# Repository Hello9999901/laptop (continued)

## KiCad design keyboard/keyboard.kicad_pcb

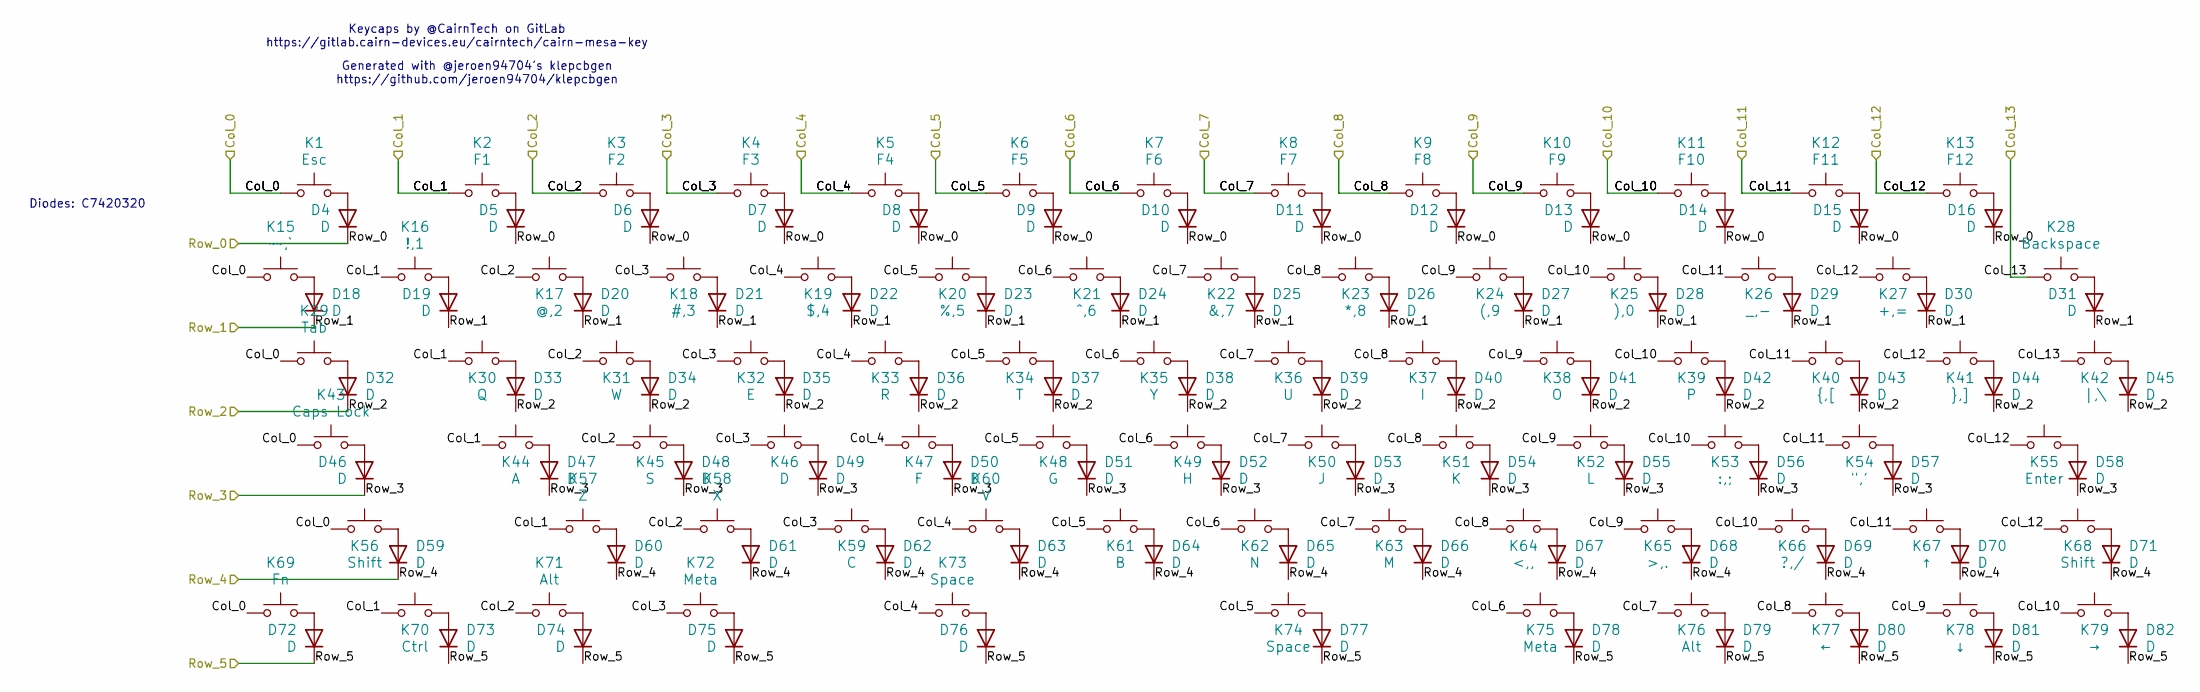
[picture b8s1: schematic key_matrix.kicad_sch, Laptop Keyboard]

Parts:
D4, D5, D6, D7, D8, D9, D10, D11, D12, D13, D14, D15, D16, D18, D19, D20, D21, D22, D23, D24, D25, D26, D27, D28, D29, D30, D31, D32, D33, D34, D35, D36, D37, D38, D39, D40, D41, D42, D43, D44, D45, D46, D47, D48, D49, D50, D51, D52, D53, D54, D55, D56, D57, D58, D59, D60, D61, D62, D63, D64, D65, D66, D67, D68, D69, D70, D71, D72, D73, D74, D75, D76, D77, D78, D79, D80, D81, D82: D; D_SOD-523
K1: Esc; Cherry_ULP_SMD
K2: F1; Cherry_ULP_SMD
K3: F2; Cherry_ULP_SMD
K4: F3; Cherry_ULP_SMD
K5: F4; Cherry_ULP_SMD
K6: F5; Cherry_ULP_SMD
K7: F6; Cherry_ULP_SMD
K8: F7; Cherry_ULP_SMD
K9: F8; Cherry_ULP_SMD
K10: F9; Cherry_ULP_SMD
K11: F10; Cherry_ULP_SMD
K12: F11; Cherry_ULP_SMD
K13: F12; Cherry_ULP_SMD
K15: ~~,`; Cherry_ULP_SMD
K16: !,1; Cherry_ULP_SMD
K17: @,2; Cherry_ULP_SMD
K18: #,3; Cherry_ULP_SMD
K19: $,4; Cherry_ULP_SMD
K20: %,5; Cherry_ULP_SMD
K21: ^,6; Cherry_ULP_SMD
K22: &,7; Cherry_ULP_SMD
K23: *,8; Cherry_ULP_SMD
K24: (,9; Cherry_ULP_SMD
K25: ),0; Cherry_ULP_SMD
K26: _,-; Cherry_ULP_SMD
K27: +,=; Cherry_ULP_SMD
K28: Backspace; Cherry_ULP_SMD
K29: Tab; Cherry_ULP_SMD
K30: Q; Cherry_ULP_SMD
K31: W; Cherry_ULP_SMD
K32: E; Cherry_ULP_SMD
K33: R; Cherry_ULP_SMD
K34: T; Cherry_ULP_SMD
K35: Y; Cherry_ULP_SMD
K36: U; Cherry_ULP_SMD
K37: I; Cherry_ULP_SMD
K38: O; Cherry_ULP_SMD
K39: P; Cherry_ULP_SMD
K40: {,[; Cherry_ULP_SMD
K41: },]; Cherry_ULP_SMD
K42: |,\; Cherry_ULP_SMD
K43: Caps Lock; Cherry_ULP_SMD
K44: A; Cherry_ULP_SMD
K45: S; Cherry_ULP_SMD
K46: D; Cherry_ULP_SMD
K47: F; Cherry_ULP_SMD
K48: G; Cherry_ULP_SMD
K49: H; Cherry_ULP_SMD
K50: J; Cherry_ULP_SMD
K51: K; Cherry_ULP_SMD
K52: L; Cherry_ULP_SMD
K53: :,;; Cherry_ULP_SMD
K54: ",'; Cherry_ULP_SMD
K55: Enter; Cherry_ULP_SMD
K56, K68: Shift; Cherry_ULP_SMD
K57: Z; Cherry_ULP_SMD
K58: X; Cherry_ULP_SMD
K59: C; Cherry_ULP_SMD
K60: V; Cherry_ULP_SMD
K61: B; Cherry_ULP_SMD
K62: N; Cherry_ULP_SMD
K63: M; Cherry_ULP_SMD
K64: <,,; Cherry_ULP_SMD
K65: >,.; Cherry_ULP_SMD
K66: ?,/; Cherry_ULP_SMD
K67: ↑; Cherry_ULP_SMD
K69: Fn; Cherry_ULP_SMD
K70: Ctrl; Cherry_ULP_SMD
K71, K76: Alt; Cherry_ULP_SMD
K72, K75: Meta; Cherry_ULP_SMD
K73, K74: Space; Cherry_ULP_SMD
K77: ←; Cherry_ULP_SMD
K78: ↓; Cherry_ULP_SMD
K79: →; Cherry_ULP_SMD

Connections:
/Key Matrix/Col_0: K1.1, K15.1, K29.1, K43.1, K56.1, K69.1; also elsewhere on the board
/Key Matrix/Col_1: K2.1, K16.1, K30.1, K44.1, K57.1, K70.1; also elsewhere on the board
/Key Matrix/Col_2: K3.1, K17.1, K31.1, K45.1, K58.1, K71.1; also elsewhere on the board
/Key Matrix/Col_3: K4.1, K18.1, K32.1, K46.1, K59.1, K72.1; also elsewhere on the board
/Key Matrix/Col_4: K5.1, K19.1, K33.1, K47.1, K60.1, K73.1; also elsewhere on the board
/Key Matrix/Col_5: K6.1, K20.1, K34.1, K48.1, K61.1, K74.1; also elsewhere on the board
/Key Matrix/Col_6: K7.1, K21.1, K35.1, K49.1, K62.1, K75.1; also elsewhere on the board
/Key Matrix/Col_7: K8.1, K22.1, K36.1, K50.1, K63.1, K76.1; also elsewhere on the board
/Key Matrix/Col_8: K9.1, K23.1, K37.1, K51.1, K64.1, K77.1; also elsewhere on the board
/Key Matrix/Col_9: K10.1, K24.1, K38.1, K52.1, K65.1, K78.1; also elsewhere on the board
/Key Matrix/Col_10: K11.1, K25.1, K39.1, K53.1, K66.1, K79.1; also elsewhere on the board
/Key Matrix/Col_11: K12.1, K26.1, K40.1, K54.1, K67.1; also elsewhere on the board
/Key Matrix/Col_12: K13.1, K27.1, K41.1, K55.1, K68.1; also elsewhere on the board
/Key Matrix/Col_13: K28.1, K42.1; also elsewhere on the board
/Key Matrix/Row_0: D4.1 (K), D5.1 (K), D6.1 (K), D7.1 (K), D8.1 (K), D9.1 (K), D10.1 (K), D11.1 (K), D12.1 (K), D13.1 (K), D14.1 (K), D15.1 (K), D16.1 (K); also elsewhere on the board
/Key Matrix/Row_1: D18.1 (K), D19.1 (K), D20.1 (K), D21.1 (K), D22.1 (K), D23.1 (K), D24.1 (K), D25.1 (K), D26.1 (K), D27.1 (K), D28.1 (K), D29.1 (K), D30.1 (K), D31.1 (K); also elsewhere on the board
/Key Matrix/Row_2: D32.1 (K), D33.1 (K), D34.1 (K), D35.1 (K), D36.1 (K), D37.1 (K), D38.1 (K), D39.1 (K), D40.1 (K), D41.1 (K), D42.1 (K), D43.1 (K), D44.1 (K), D45.1 (K); also elsewhere on the board
/Key Matrix/Row_3: D46.1 (K), D47.1 (K), D48.1 (K), D49.1 (K), D50.1 (K), D51.1 (K), D52.1 (K), D53.1 (K), D54.1 (K), D55.1 (K), D56.1 (K), D57.1 (K), D58.1 (K); also elsewhere on the board
/Key Matrix/Row_4: D59.1 (K), D60.1 (K), D61.1 (K), D62.1 (K), D63.1 (K), D64.1 (K), D65.1 (K), D66.1 (K), D67.1 (K), D68.1 (K), D69.1 (K), D70.1 (K), D71.1 (K); also elsewhere on the board
/Key Matrix/Row_5: D72.1 (K), D73.1 (K), D74.1 (K), D75.1 (K), D76.1 (K), D77.1 (K), D78.1 (K), D79.1 (K), D80.1 (K), D81.1 (K), D82.1 (K); also elsewhere on the board
unnamed: D4.2 (A), K1.2
unnamed: D5.2 (A), K2.2
unnamed: D6.2 (A), K3.2
unnamed: D7.2 (A), K4.2
unnamed: D8.2 (A), K5.2
unnamed: D9.2 (A), K6.2
unnamed: D10.2 (A), K7.2
unnamed: D11.2 (A), K8.2
unnamed: D12.2 (A), K9.2
unnamed: D13.2 (A), K10.2
unnamed: D14.2 (A), K11.2
unnamed: D15.2 (A), K12.2
unnamed: D16.2 (A), K13.2
unnamed: D18.2 (A), K15.2
unnamed: D19.2 (A), K16.2
unnamed: D20.2 (A), K17.2
unnamed: D21.2 (A), K18.2
unnamed: D22.2 (A), K19.2
unnamed: D23.2 (A), K20.2
unnamed: D24.2 (A), K21.2
unnamed: D25.2 (A), K22.2
unnamed: D26.2 (A), K23.2
unnamed: D27.2 (A), K24.2
unnamed: D28.2 (A), K25.2
unnamed: D29.2 (A), K26.2
unnamed: D30.2 (A), K27.2
unnamed: D31.2 (A), K28.2
unnamed: D32.2 (A), K29.2
unnamed: D33.2 (A), K30.2
unnamed: D34.2 (A), K31.2
unnamed: D35.2 (A), K32.2
unnamed: D36.2 (A), K33.2
unnamed: D37.2 (A), K34.2
unnamed: D38.2 (A), K35.2
unnamed: D39.2 (A), K36.2
unnamed: D40.2 (A), K37.2
unnamed: D41.2 (A), K38.2
unnamed: D42.2 (A), K39.2
unnamed: D43.2 (A), K40.2
unnamed: D44.2 (A), K41.2
unnamed: D45.2 (A), K42.2
unnamed: D46.2 (A), K43.2
unnamed: D47.2 (A), K44.2
unnamed: D48.2 (A), K45.2
unnamed: D49.2 (A), K46.2
unnamed: D50.2 (A), K47.2
unnamed: D51.2 (A), K48.2
unnamed: D52.2 (A), K49.2
unnamed: D53.2 (A), K50.2
unnamed: D54.2 (A), K51.2
unnamed: D55.2 (A), K52.2
unnamed: D56.2 (A), K53.2
unnamed: D57.2 (A), K54.2
unnamed: D58.2 (A), K55.2
unnamed: D59.2 (A), K56.2
unnamed: D60.2 (A), K57.2
unnamed: D61.2 (A), K58.2
unnamed: D62.2 (A), K59.2
unnamed: D63.2 (A), K60.2
unnamed: D64.2 (A), K61.2
unnamed: D65.2 (A), K62.2
unnamed: D66.2 (A), K63.2
unnamed: D67.2 (A), K64.2
unnamed: D68.2 (A), K65.2
unnamed: D69.2 (A), K66.2
unnamed: D70.2 (A), K67.2
unnamed: D71.2 (A), K68.2
unnamed: D72.2 (A), K69.2
unnamed: D73.2 (A), K70.2
unnamed: D74.2 (A), K71.2
unnamed: D75.2 (A), K72.2
unnamed: D76.2 (A), K73.2
unnamed: D77.2 (A), K74.2
unnamed: D78.2 (A), K75.2
unnamed: D79.2 (A), K76.2
unnamed: D80.2 (A), K77.2
unnamed: D81.2 (A), K78.2
unnamed: D82.2 (A), K79.2

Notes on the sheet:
Diodes: C7420320
Generated with @jeroen94704's klepcbgen https://github.com/jeroen94704/klepcbgen
Keycaps by @CairnTech on GitLab https://gitlab.cairn-devices.eu/cairntech/cairn-mesa-key

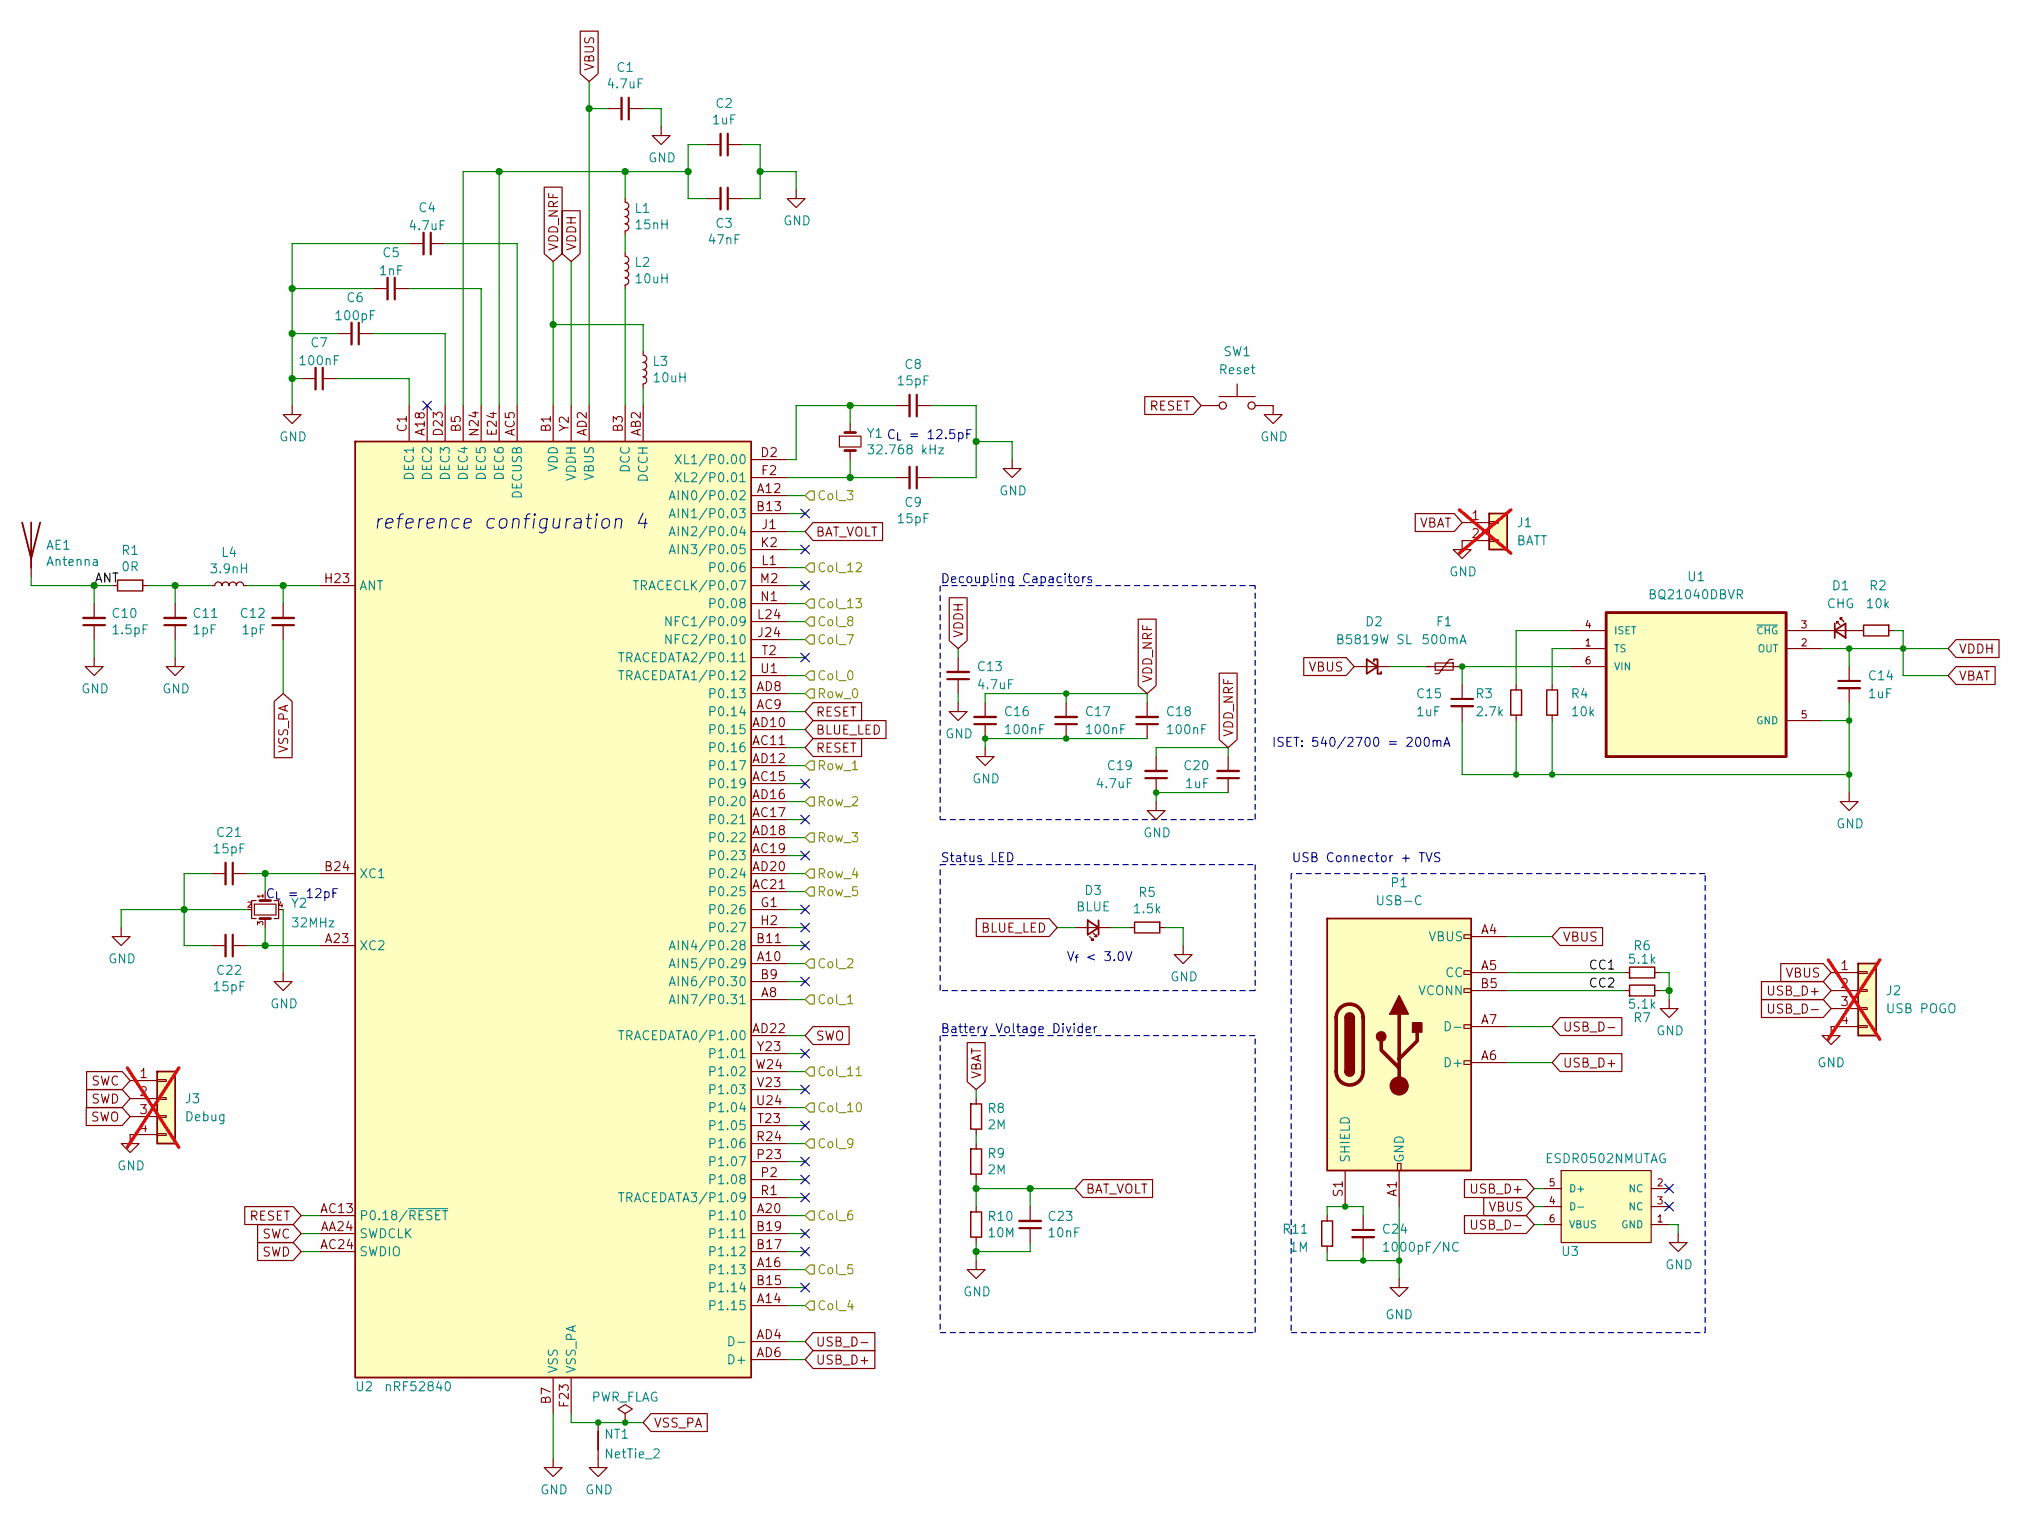
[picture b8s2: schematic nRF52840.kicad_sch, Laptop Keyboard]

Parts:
AE1: Antenna; 2.4GHz-meander-antenna-v2
C1, C4, C13, C19: 4.7uF; C_0402_1005Metric; Manufacturer Part CL05A475KP5NRNC; LCSC Part C368809
C2, C14, C15, C20: 1uF; C_0402_1005Metric; Manufacturer Part CL05A105KO5NNNC; LCSC Part C52923
C3: 47nF; C_0402_1005Metric; Manufacturer Part CL05B473KO5NNNC; LCSC Part C307434
C5: 1nF; C_0402_1005Metric; Manufacturer Part CL05B102KB5NNNC; LCSC Part C14442
C6: 100pF; C_0402_1005Metric; Manufacturer Part CL05C101JB5NNNC; LCSC Part C26409
C7, C16, C17, C18: 100nF; C_0402_1005Metric; Manufacturer Part CL05B104KA5NNNC; LCSC Part C1525
C8, C9, C21, C22: 15pF; C_0402_1005Metric; Manufacturer Part CL05C150JB51PNC; LCSC Part C307341
C10: 1.5pF; C_0402_1005Metric; Manufacturer Part CL05C1R5CB5NNNC; LCSC Part C170150
C11, C12: 1pF; C_0402_1005Metric; Manufacturer Part CL05C010CB5NNNC; LCSC Part C371977
C23: 10nF; C_0402_1005Metric; Manufacturer Part CL05B103KB5NNNC; LCSC Part C15195
C24: 1000pF/NC; C_0402_1005Metric
D1: CHG; LED_0603_1608Metric; Manufacturer Part 19-217/S2C-AQ1R1B/3T; LCSC Part C160478
D2: B5819W SL; D_SOD-323; Manufacturer Part PMEG4010CEJ; LCSC Part C50704
D3: BLUE; LED_0603_1608Metric; Manufacturer Part 19-217/BHC-ZL1M2RY/3T; LCSC Part C146215
F1: 500mA; Fuse_0402_1005Metric; Manufacturer Part 0402L050SLKR; LCSC Part C206938
J1: BATT; PinHeader_1x02_P2.54mm_Vertical; not fitted
J2: USB POGO; PinHeader_1x04_P2.54mm_Vertical; not fitted
J3: Debug; PinHeader_1x04_P2.54mm_Vertical; not fitted
L1: 15nH; L_0402_1005Metric; Manufacturer Part MLG1005S15NJT000; LCSC Part C76763
L2, L3: 10uH; L_0603_1608Metric; Manufacturer Part MLF1608E100KTD00; LCSC Part C76732
L4: 3.9nH; L_0402_1005Metric; Manufacturer Part MLG1005S3N9BT000; LCSC Part C76775
NT1: NetTie_2; net-tie-2-tiny
P1: USB-C; USB_C_Receptacle_HRO_TYPE-C-31-M-12
R1: 0R; R_0402_1005Metric; Manufacturer Part RC0402FR-070RL; LCSC Part C106231
R2, R4: 10k; R_0402_1005Metric; Manufacturer Part RC0402FR-0710KL; LCSC Part C60490
R3: 2.7k; R_0402_1005Metric; Manufacturer Part RC0402FR-0710KL; LCSC Part C60490
R5: 1.5k; R_0402_1005Metric; Manufacturer Part RC0402FR-071K5L; LCSC Part C114759
R6, R7: 5.1k; R_0402_1005Metric; Manufacturer Part RC0402FR-075K1L; LCSC Part C105872
R8, R9: 2M; R_0402_1005Metric; Manufacturer Part RC0402FR-072ML; LCSC Part C138014
R10: 10M; R_0402_1005Metric; Manufacturer Part RC0402FR-0710ML; LCSC Part C138067
R11: 1M; R_0402_1005Metric
SW1: Reset; SW_Push_1P1T_XKB_TS-1187A
U1: BQ21040DBVR; SOT95P280X145-6N
U2: nRF52840; Nordic_AQFN-73-1EP_7x7mm_P0.5mm; Manufacturer Part NRF52840-QIAA-R; LCSC Part C1851953
U3: ESDR0502NMUTAG; UDFN-6_1.2x1.0mm_P0.4mm; Manufacturer Part ESDR0502NMUTBG; LCSC Part C327480
Y1: 32.768 kHz; Crystal_SMD_2012-2Pin_2.0x1.2mm; Manufacturer Part SC20S-12.5PF20PPM; LCSC Part C97607
Y2: 32MHz; Crystal_SMD_2016-4Pin_2.0x1.6mm; Manufacturer Part Q22FA1280001800; LCSC Part C2965584

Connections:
/Key Matrix/Col_0: U2.U1 (TRACEDATA1/P0.12); also elsewhere on the board
/Key Matrix/Col_1: U2.A8 (AIN7/P0.31); also elsewhere on the board
/Key Matrix/Col_2: U2.A10 (AIN5/P0.29); also elsewhere on the board
/Key Matrix/Col_3: U2.A12 (AIN0/P0.02); also elsewhere on the board
/Key Matrix/Col_4: U2.A14 (P1.15); also elsewhere on the board
/Key Matrix/Col_5: U2.A16 (P1.13); also elsewhere on the board
/Key Matrix/Col_6: U2.A20 (P1.10); also elsewhere on the board
/Key Matrix/Col_7: U2.J24 (NFC2/P0.10); also elsewhere on the board
/Key Matrix/Col_8: U2.L24 (NFC1/P0.09); also elsewhere on the board
/Key Matrix/Col_9: U2.R24 (P1.06); also elsewhere on the board
/Key Matrix/Col_10: U2.U24 (P1.04); also elsewhere on the board
/Key Matrix/Col_11: U2.W24 (P1.02); also elsewhere on the board
/Key Matrix/Col_12: U2.L1 (P0.06); also elsewhere on the board
/Key Matrix/Col_13: U2.N1 (P0.08); also elsewhere on the board
/Key Matrix/Row_0: U2.AD8 (P0.13); also elsewhere on the board
/Key Matrix/Row_1: U2.AD12 (P0.17); also elsewhere on the board
/Key Matrix/Row_2: U2.AD16 (P0.20); also elsewhere on the board
/Key Matrix/Row_3: U2.AD18 (P0.22); also elsewhere on the board
/Key Matrix/Row_4: U2.AD20 (P0.24); also elsewhere on the board
/Key Matrix/Row_5: U2.AC21 (P0.25); also elsewhere on the board
/nRF52840/ANT: AE1.1 (A), C10.2, R1.2
/nRF52840/CC1: P1.A5 (CC), R6.1
/nRF52840/CC2: P1.B5 (VCONN), R7.1
BAT_VOLT: C23.2, R9.2, R10.1, U2.J1 (AIN2/P0.04)
BLUE_LED: D3.2 (A), U2.AD10 (P0.15)
GND: C1.1, C2.1, C3.1, C4.2, C5.2, C6.2, C7.2, C8.1, C9.1, C10.1, C11.1, C13.1, C14.2, C15.2, C16.1, C17.1, C18.1, C19.1, C20.1, C21.2, C22.2, C23.1, C24.2, J1.2, J2.4, J3.4, NT1.2, P1.A1 (GND), P1.A12 (GND), P1.B1 (GND), P1.B12 (GND), R3.1, R4.1, R5.1, R6.2, R7.2, R10.2, R11.1, SW1.2, U1.5 (GND), U2.B7 (VSS), U2.EP (VSS), U3.1 (GND), Y2.2, Y2.4
unnamed: C11.2, L4.1, R1.1
unnamed: D1.2 (A), R2.2
unnamed: D1.1 (K), U1.3 (~CHG)
unnamed: D2.1 (K), F1.2
unnamed: D3.1 (K), R5.2
unnamed: L1.2, L2.1
unnamed: C24.1, P1.S1 (SHIELD), R11.2
unnamed: R8.2, R9.1
unnamed: R3.2, U1.4 (ISET)
unnamed: R4.2, U1.1 (TS)
unnamed: C15.1, F1.1, U1.6 (VIN)
unnamed: C12.2, L4.2, U2.H23 (ANT)
unnamed: L2.2, U2.B3 (DCC)
unnamed: L3.2, U2.AB2 (DCCH)
unnamed: C7.1, U2.C1 (DEC1)
unnamed: C6.1, U2.D23 (DEC3)
unnamed: C2.2, C3.2, L1.1, U2.B5 (DEC4), U2.E24 (DEC6)
unnamed: C5.1, U2.N24 (DEC5)
unnamed: C4.1, U2.AC5 (DECUSB)
unnamed: C21.1, U2.B24 (XC1), Y2.1
unnamed: C22.1, U2.A23 (XC2), Y2.3
unnamed: C8.2, U2.D2 (XL1/P0.00), Y1.1
unnamed: C9.2, U2.F2 (XL2/P0.01), Y1.2
RESET: SW1.1, U2.AC9 (P0.14), U2.AC11 (P0.16), U2.AC13 (P0.18/~RESET)
SWC: J3.1, U2.AA24 (SWDCLK)
SWD: J3.2, U2.AC24 (SWDIO)
SWO: J3.3, U2.AD22 (TRACEDATA0/P1.00)
USB_D+: J2.2, P1.A6 (D+), P1.B6 (D+), U2.AD6 (D+), U3.5 (D+)
USB_D-: J2.3, P1.A7 (D-), P1.B7 (D-), U2.AD4 (D-), U3.6 (VBUS)
VBAT: C13.2, C14.1, J1.1, R2.1, R8.1, U1.2 (OUT), U2.Y2 (VDDH)
VBUS: C1.2, D2.2 (A), J2.1, P1.A4 (VBUS), P1.A9 (VBUS), P1.B4 (VBUS), P1.B9 (VBUS), U2.AD2 (VBUS), U3.4 (D-)
VDD_NRF: C16.2, C17.2, C18.2, C19.2, C20.2, L3.1, U2.A22 (VDD), U2.AD14 (VDD), U2.AD23 (VDD), U2.B1 (VDD), U2.W1 (VDD)
VSS_PA: C12.1, NT1.1, U2.F23 (VSS_PA)

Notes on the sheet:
C_{L} = 12pF
C_{L} = 12.5pF
Battery Voltage Divider
ISET: 540/2700 = 200mA
Decoupling Capacitors
USB Connector + TVS
reference configuration 4
Status LED
V_{f} < 3.0V

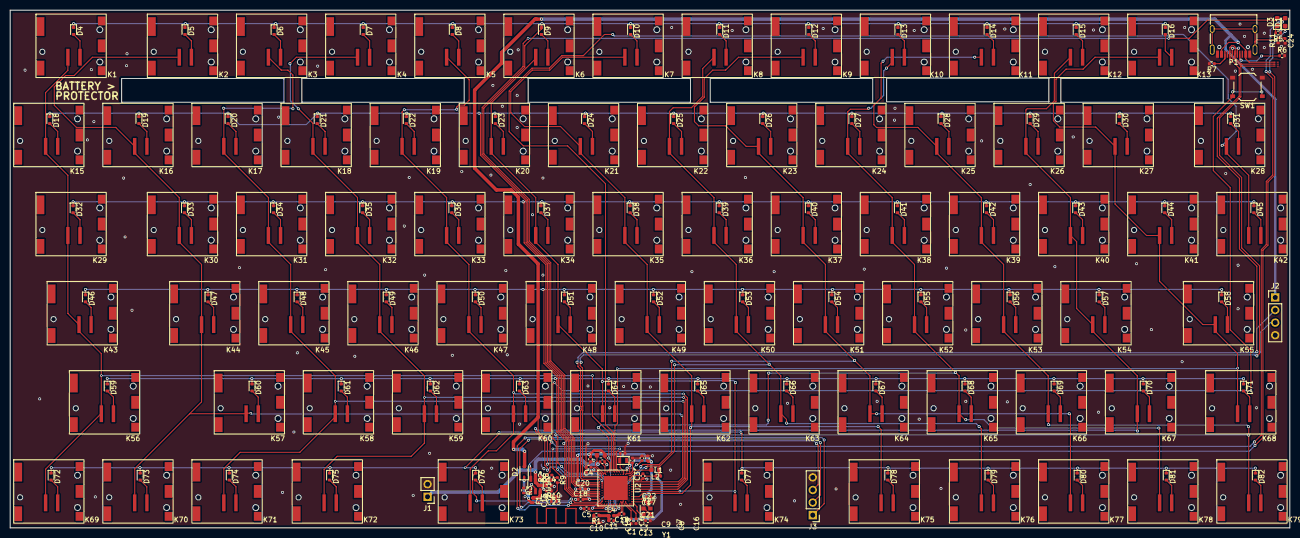
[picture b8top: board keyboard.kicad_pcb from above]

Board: 2 copper layers, 258.4 x 104.6 mm, 211 parts (0 on the bottom side), 137 nets.

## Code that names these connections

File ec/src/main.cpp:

#include <Wire.h>
#include <Arduino.h>
#include "Adafruit_HUSB238.h"
#include "LTC2943.h"
#include "BQ25713.h"
#include <EEPROM.h>

#define LED1 12
#define LED2 13
#define LED3 14
#define LED4 15
#define LED5 16

#define BQ25713_IBAT 11
#define BQ25713_IADPT 10
#define BQ77915_CBI 9
#define BQ77915_PRES 8
#define BQ25713_CMPOUT 7
#define BQ25713_EN_OTG 6
#define BQ25713_CHRG_OK 5
#define BQ25713_PROCHOT_N 4
#define LTC2943_ALCC 3

Adafruit_HUSB238 husb238;

uint16_t charge;
uint16_t current;
uint16_t temperature;
uint16_t voltage;

// Function to read a 16-bit register
uint16_t readRegister(uint8_t reg)
{
    Wire.beginTransmission(BQ25713_ADDRESS);
    Wire.write(reg); // Send register address
    Wire.endTransmission(false);

    Wire.requestFrom(BQ25713_ADDRESS, 1);
    return Wire.read(); // Combine high and low byte
}

void debugPrint(String info, uint8_t data)
{
    Serial.print(info);
    Serial.print("0x");
    Serial.print(data, HEX);
    Serial.print(", 0b");
    Serial.print(data, BIN);
    Serial.print(", ");
    Serial.print(data, DEC);
    Serial.println();
    Serial.println();
}

// Function to write a 16-bit value to consecutive I2C registers
void writeRegister16(uint8_t lsbReg, uint16_t data)
{
    Wire.beginTransmission(BQ25713_ADDRESS);
    Wire.write(lsbReg + 1);         // Write to MSB register first
    Wire.write((data >> 8) & 0xFF); // Write MSB
    Wire.endTransmission();

    Wire.beginTransmission(BQ25713_ADDRESS);
    Wire.write(lsbReg);      // Write to LSB register
    Wire.write(data & 0xFF); // Write LSB
    Wire.endTransmission();
}

void chargingInit()
{
    // 0x020E to register 0x00
    writeRegister16(CHARGEOPTION0_LSB, 0x820E);

    // charging
    writeRegister16(CHARGECURRENT_LSB, 0x0800);
}

void dimLED(int batteryPercent)
{
    static int brightness = 0;
    static int fadeAmount = 5;
    static unsigned long lastDimTime = 0;

    unsigned long currentTime = micros(); // Use micros() for more precise timing

    // Check if enough time has passed since last dimming
    if (currentTime - lastDimTime >= 30000)
    { // 20ms = 20,000 microseconds
        lastDimTime = currentTime;

        // Change the brightness
        brightness += fadeAmount;

        // Reverse the fade direction when we reach the limits
        if (brightness <= 0 || brightness >= 255)
        {
            fadeAmount = -fadeAmount;
        }

        // Set the LED brightness
        if (batteryPercent > 90) {
            analogWrite(LED3, brightness);
            analogWrite(LED4, brightness);
            analogWrite(LED5, brightness);
        }
        else if (batteryPercent > 60) {
            analogWrite(LED3, brightness);
            analogWrite(LED4, brightness);
            digitalWrite(LED5, LOW);
        }
        else if (batteryPercent > 30) {
            analogWrite(LED3, brightness);
            digitalWrite(LED4, LOW);
            digitalWrite(LED5, LOW);
        }
    }
}

void setup()
{
    Serial.begin(115200);
    Wire.begin(2, 1);
    EEPROM.begin(512); // half kb simulated flash

    pinMode(LED1, OUTPUT);
    pinMode(LED2, OUTPUT);
    pinMode(LED3, OUTPUT);
    pinMode(LED4, OUTPUT);
    pinMode(LED5, OUTPUT);

    digitalWrite(LED1, LOW);
    digitalWrite(LED2, LOW);
    digitalWrite(LED3, LOW);
    digitalWrite(LED4, LOW);
    digitalWrite(LED5, LOW);

    LTC2943_write(LTC2943_I2C_ADDRESS, LTC2943_CONTROL_REG, (LTC2943_AUTOMATIC_MODE | LTC2943_PRESCALAR_M_4096));

    chargingInit();

    delay(1000);

    Serial.println("EEPROM Stored Value: ");
    Serial.println(EEPROM.read(0));
    uint16_t storedCharge = (EEPROM.read(0) << 8) | EEPROM.read(1);
    Serial.println(storedCharge);

    LTC2943_write_16_bits(LTC2943_I2C_ADDRESS, LTC2943_ACCUM_CHARGE_MSB_REG, storedCharge);
}

bool vbusConnected = false;
int previousTime = 0;
int batteryPercent = 100;
bool charging = false;

void loop()
{
    if (millis() - previousTime >= 1000)
    {
        previousTime = millis();
        Serial.println(F("----------------------------------------------"));

        Wire.beginTransmission(HUSB238_I2CADDR_DEFAULT);
        int transmissionResult = Wire.endTransmission();

        Serial.print("HUSB Connected: ");
        Serial.println(transmissionResult == 0 ? "true" : "false");

        if (transmissionResult == 0 && !vbusConnected)
        {
            delay(500);

            husb238.begin(HUSB238_I2CADDR_DEFAULT, &Wire);
            husb238.selectPD(PD_SRC_20V);
            husb238.requestPD();

            Serial.println("REQUESTED 20V");
            Serial.println(husb238.isVoltageDetected(PD_SRC_20V));

            delay(100);
            chargingInit();

            vbusConnected = true;
        }
        else if (vbusConnected && transmissionResult != 0)
        {
            vbusConnected = false;
        }

        Serial.print("VBUS Connected: ");
        Serial.println(vbusConnected);

        Wire.beginTransmission(BQ25713_ADDRESS);
        transmissionResult = Wire.endTransmission();

        if (transmissionResult == 0)
        {
            Serial.print("VBUS: ");
            Serial.println(readRegister(0x27) * 0.064);
            Serial.print("VSYS: ");
            Serial.println(readRegister(0x2D) * 0.064);
            Serial.print("VBAT: ");
            Serial.println(readRegister(0x2C) * 0.064);

            Serial.print("CHARGING: ");
            if (readRegister(0x29) > 0)
            {
                Serial.println("YES");
                charging = true;
            }
            else
            {
                Serial.println("NO");
                charging = false;
            }
        }
        else
        {
            Serial.println("BQ25713 NOT CONNECTED");
        }

        // debugPrint("ChargerStatus 0x21:", readRegister(0x21));
        // debugPrint("ChargerStatus 0x20:", readRegister(0x20));
        // debugPrint("ChargeOption0 0x01:", readRegister(0x01));
        // debugPrint("ChargeOption0 0x00:", readRegister(0x00));
        // debugPrint("ChargeCurrent 0x03:", readRegister(0x03));
        // debugPrint("ChargeCurrent 0x02:", readRegister(0x02));
        // debugPrint("ADCOptions 0x3B:", readRegister(0x3B));
        // debugPrint("ADCOptions 0x3A:", readRegister(0x3A));
        // debugPrint("IIN_HOST 0x0F:", readRegister(IIN_HOST_MSB));
        // debugPrint("Input Current:", readRegister(ADCIINCMPIN_MSB));
        // debugPrint("CMP Voltage:", readRegister(ADCIINCMPIN_LSB));

        // debugPrint("PSYS 0x26:", readRegister(0x26));
        // debugPrint("ICHG 0x29:", readRegister(0x29));
        // debugPrint("IDCHG 0x28:", readRegister(0x28));

        LTC2943_read_16_bits(LTC2943_I2C_ADDRESS, LTC2943_VOLTAGE_MSB_REG, &voltage);
        Serial.print("VOLT: ");
        Serial.println(LTC2943_code_to_voltage(voltage), 4);

        LTC2943_read_16_bits(LTC2943_I2C_ADDRESS, LTC2943_ACCUM_CHARGE_MSB_REG, &charge);
        Serial.print("CHRG mAh: ");
        Serial.println(LTC2943_code_to_mAh(charge, 0.01, 4096), 4);

        if (charge > 0x9C4)
        {
            charge = 0x9C4;
            LTC2943_write_16_bits(LTC2943_I2C_ADDRESS, LTC2943_ACCUM_CHARGE_MSB_REG, charge);
        }

        EEPROM.write(0, (charge >> 8) & 0xFF); // Write high byte
        EEPROM.write(1, charge & 0xFF);        // Write low byte
        EEPROM.commit();

        LTC2943_read_16_bits(LTC2943_I2C_ADDRESS, LTC2943_CURRENT_MSB_REG, &current);
        Serial.print("CURR: ");
        Serial.println(LTC2943_code_to_current(current, 0.01), 4);

        LTC2943_read_16_bits(LTC2943_I2C_ADDRESS, LTC2943_TEMPERATURE_MSB_REG, &temperature);
        Serial.print("TEMP: ");
        Serial.println(LTC2943_code_to_celcius_temperature(temperature), 4);

        Serial.print("BATTERY PERCENT: ");
        batteryPercent = (LTC2943_code_to_mAh(charge, 0.01, 4096) * 100 / (float)4250);
        Serial.println(batteryPercent);

        if (LTC2943_code_to_celcius_temperature(temperature) >= 60)
        {
            // thermal shutdown
            writeRegister16(CHARGECURRENT_LSB, 0x0000);
        }
        else
        {
            // charging
            writeRegister16(CHARGECURRENT_LSB, 0x0800);
        }
    }

    if (charging) {
        dimLED(batteryPercent);
    }
    else {
        if (batteryPercent > 90) {
            digitalWrite(LED3, HIGH);
            digitalWrite(LED4, HIGH);
            digitalWrite(LED5, HIGH);
        }
        else if (batteryPercent > 60) {
            digitalWrite(LED3, HIGH);
            digitalWrite(LED4, HIGH);
            digitalWrite(LED5, LOW);
        }
        else if (batteryPercent > 30) {
            digitalWrite(LED3, HIGH);
            digitalWrite(LED4, LOW);
            digitalWrite(LED5, LOW);
        }
    }
}

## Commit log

2024-06-01 init
2024-06-03 keyboard v1 halfway routed
2024-06-03 fully routed and fixed
2024-06-07 trackpad solutions
2024-06-12 anyon e
2024-06-12 motherboard initial pinout and research
2024-06-12 added lock files to gitignore
2024-06-12 added purchase link to eol'ed trackpad
2024-06-12 added kicad language attributes
2024-06-26 created haptic project
2024-06-26 hdmi, edp, peripheral implementations
2024-06-26 wip with pcie2.0 e key, ethernet, buttons and more
2024-06-26 haptics wip, created encoder pcb
2024-06-29 implemented most features
2024-06-29 initialized power system
2024-07-02 major power work
2024-07-03 CAD work + documentation
2024-07-06 full cm3588 sym + fp + 3d
2024-07-06 synchronizing hierarchical pins
2024-07-07 linked all footprints
2024-07-07 cost optimizations for jlc
2024-07-08 added labeled pdfs for documentation
2024-07-08 uploaded cm3588 3d model, working on audio
2024-07-08 added color to model
2024-07-08 audio done
2024-07-09 motherboard schematic done
2024-07-11 work preparing for routing
2024-07-11 added website
2024-07-11 added vercel configs
2024-07-11 Create LICENSE
2024-07-12 optimized website
2024-07-12 added mission + finalized website
    Delete rss.xml.ts
2024-07-16 keyboard battery and pogo pin system
2024-07-16 minor motherboard work
2024-07-16 initial motherboard layout!
2024-07-16 component placement of I/O
2024-07-17 placement roughly halfway done
2024-07-17 implemented progress on website
2024-07-27 layout nearing completion
2024-07-29 removed 2.5G ethernet
2024-07-31 created display evaluation board + layout modifications
2024-07-31 updated progress on website
2024-08-01 TAPEOUT: keyboard + protector, display + halls switch eval
2024-08-05 keyboard TAPEOUT and plate file finalization
2024-08-05 motherboard net labeling and impedance matching
2024-08-08 motherboard routing work
2024-08-08 added bootloader repo submodule
    added bootloader repo submodule
    Create Adafruit_nRF52_Bootloader
    Update Adafruit_nRF52_Bootloader
2024-08-09 updated website for keyboard v1
2024-08-11 updated website main page
2024-08-11 routing work
2024-08-19 added two more display eval test boards
2024-08-21 starting motherboard v0.2
    lessons from display eval v1
2024-08-21 v0.2 layout
2024-08-22 6 layer for better high speed signaling integrity
2024-08-22 rerouting high speed traces
2024-08-23 v0.2 progress
2024-08-23 testing vercel website build trigger
2024-08-24 v0.2 good routing checkpoint (217 unrouted)
2024-08-25 v0.2 75 routes left!
2024-08-25 v0.2 < 50 unrouted
2024-08-27 v0.2 routing complete
2024-08-28 v0.2 almost ready for tapeout
2024-08-28 v0.2 silkscreen design
2024-08-30 v0.2 submitted to production
2024-09-03 functioning display update
2024-09-11 powertrain schematic init
2024-09-16 mainboard v0.3 + power WIP
2024-09-16 power v0.1 layout done
2024-09-17 power sub 50 routes
2024-09-17 updates for web
2024-09-18 keyboard v1 complete
2024-09-18 routing complete
    routing complete
2024-09-20 silkscreening power
2024-09-21 powertrain pcb v0.1 complete
2024-09-21 final tapeout
2024-10-05 motherboard 3d file
2024-10-05 embedded controller work
    Update power.kicad_sch
2024-10-05 power 3d file
2024-10-05 powertrain blog update
2024-10-06 powertrain v2
2024-10-07 powertrain v0.2 tapeout
2024-10-08 fixed pt v0.2 inductor
2024-10-14 preparing for motherboard v1.1
2024-10-23 EC working!
2024-10-24 cleanup and final mainboard tapeout
2024-10-24 website updates
2024-10-27 v1.0 tapeout and more
2024-10-29 taped out switch and audio pcbs
2024-10-29 progress updates
2024-10-29 fixed typo
2024-10-31 powertrain charging functional (balancing difficult to test)
2024-10-31 powertrain charging update
2024-11-16 working on ec fixes
2024-11-17 about to present!
2025-01-03 about to present!
    about to present!
2025-01-19 working on new blog
2025-01-19 test?
2025-01-20 blog done
2025-01-22 blog final touches
2025-01-22 open release
2025-01-23 fix cad link
2025-01-23 fix: Added .md to file name to render properly on GH + fixed word redundancy in content
2025-01-23 fix: README file name fix + content fix for code block
2025-01-23 bug fix: thermal degree detection typo creates unrechable if-statement
2025-02-06 Add YouTube video link to README.md
2025-02-06 Fix YouTube thumbnail aspect ratio in README.md
2025-02-28 Update Header.astro
    Remove `target='_blank'` attribute from navigation links in Header.astro to prevent opening links in new tabs, enhancing user experience.
2025-04-01 Update consts.ts
    Update consts.ts
